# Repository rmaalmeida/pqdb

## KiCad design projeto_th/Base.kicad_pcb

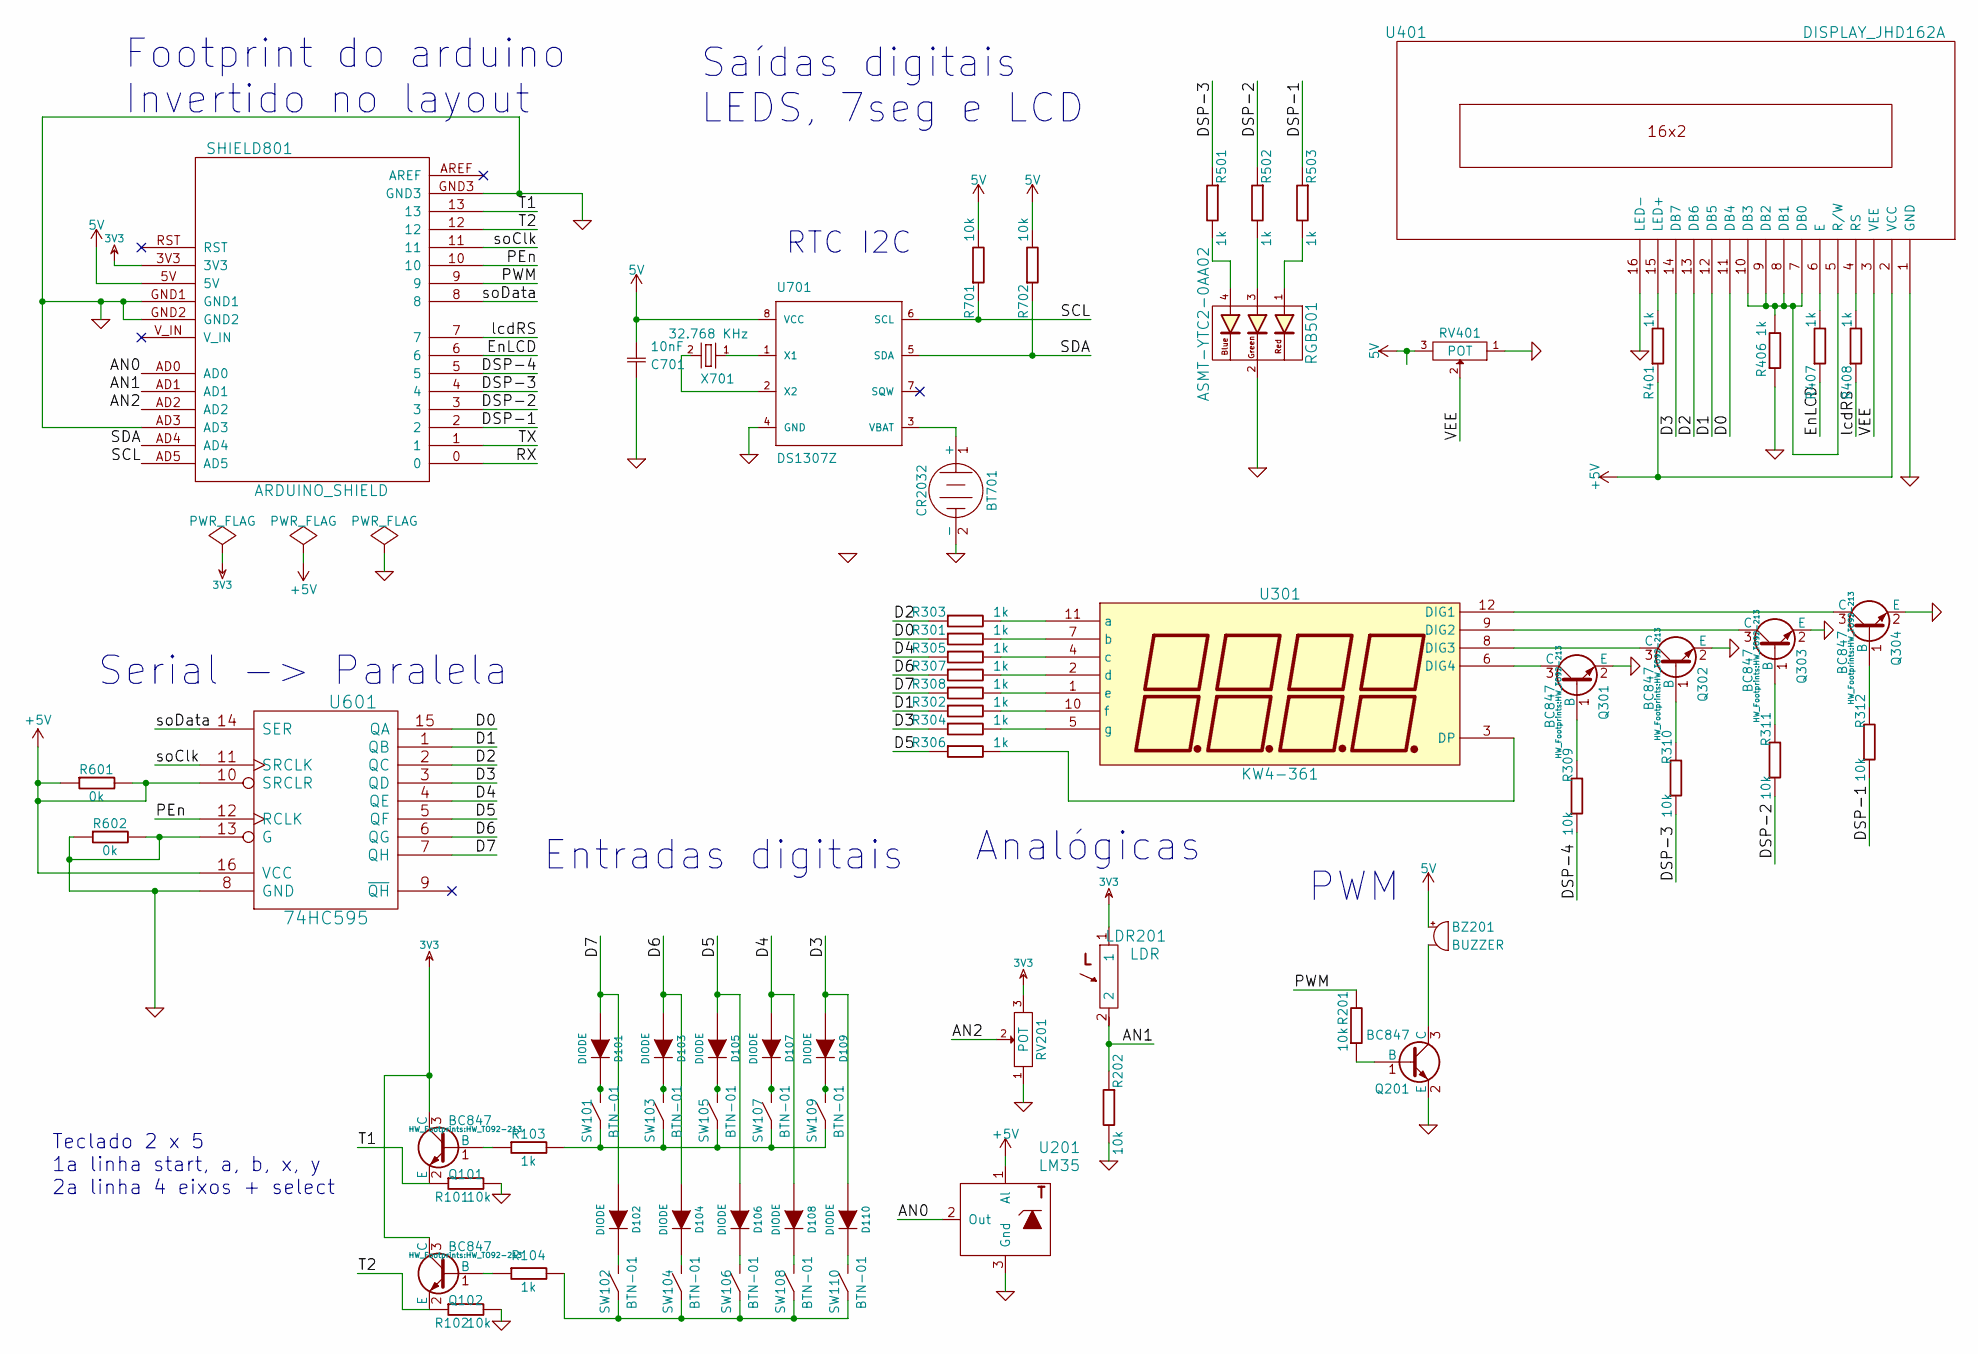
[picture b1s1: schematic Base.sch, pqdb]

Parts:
BT701: CR2032; HW_CR2032H
BZ201: BUZZER; HW_Buzzer
C701: 10nF; HW_CAPACITOR
D101, D102, D103, D104, D105, D106, D107, D108, D109, D110: DIODE; D5
LDR201: LDR; HW_LDR
Q101, Q102, Q201, Q301, Q302, Q303, Q304: BC847; HW_TO92-213
R101, R102, R201, R202, R309, R310, R311, R312, R701, R702: 10k; HW_Resistor
R103, R104, R301, R302, R303, R304, R305, R306, R307, R308, R401, R406, R407, R408, R501, R502, R503: 1k; HW_Resistor
R601, R602: 0k; Resistor_Horizontal_RM15mm
RGB501: ASMT-YTC2-0AA02; HW_LED-5MM-RGB
RV201, RV401: POT; HW_Potenciometro_2
SHIELD801: ARDUINO_SHIELD; ARDUINO_SHIELD_2
SW101, SW102, SW103, SW104, SW105, SW106, SW107, SW108, SW109, SW110: BTN-01; HW_Switch_tactil_adaptada
U201: LM35; HW_TO92-123
U301: KW4-361; HW_Disp_7seg_4dig
U401: DISPLAY_JHD162A; HW_LCD
U601: 74HC595; HW_DIP-16__300_ELL
U701: DS1307Z; HW_DIP-8
X701: 32.768 KHz; HW_Crystal_32768

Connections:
3V3: LDR201.1, Q101.3 (C), Q102.3 (C), RV201.3, SHIELD801.3V3
/AN0: SHIELD801.AD0, U201.2 (Out)
/AN1: LDR201.2, R202.1, SHIELD801.AD1
/AN2: RV201.2, SHIELD801.AD2
/D0: R301.1, U401.11 (DB4), U601.15 (QA)
/D1: R302.1, U401.12 (DB5), U601.1 (QB)
/D2: R303.1, U401.13 (DB6), U601.2 (QC)
/D3: D109.1 (A), D110.1 (A), R304.1, U401.14 (DB7), U601.3 (QD)
/D4: D107.1 (A), D108.1 (A), R305.1, U601.4 (QE)
/D5: D105.1 (A), D106.1 (A), R306.1, U601.5 (QF)
/D6: D103.1 (A), D104.1 (A), R307.1, U601.6 (QG)
/D7: D101.1 (A), D102.1 (A), R308.1, U601.7 (QH)
/DSP-1: R312.1, R503.1, SHIELD801.2
/DSP-2: R311.1, R502.1, SHIELD801.3
/DSP-3: R310.1, R501.1, SHIELD801.4
/DSP-4: R309.1, SHIELD801.5
/EnLCD: R407.1, SHIELD801.6
/PEn: SHIELD801.10, U601.12 (RCLK)
/PWM: R201.2, SHIELD801.9
/RX: SHIELD801.0
/SCL: R701.1, SHIELD801.AD5, U701.6 (SCL)
/SDA: R702.1, SHIELD801.AD4, U701.5 (SDA)
/T1: Q101.2 (E), R101.1, SHIELD801.13
/T2: Q102.2 (E), R102.1, SHIELD801.12
/TX: SHIELD801.1
/VEE: RV401.2, U401.3 (VEE)
/lcdRS: R408.1, SHIELD801.7
/soClk: SHIELD801.11, U601.11 (SRCLK)
/soData: SHIELD801.8, U601.14 (SER)
GND: BT701.2 (-), C701.1, Q201.2 (E), Q301.2 (E), Q302.2 (E), Q303.2 (E), Q304.2 (E), R101.2, R102.2, R202.2, R406.1, R602.1, R602.2, RGB501.2 (KG), RV201.1, RV401.1, SHIELD801.AD3, SHIELD801.GND1, SHIELD801.GND2, SHIELD801.GND3, U201.3 (Gnd), U401.1 (GND), U401.16 (LED-), U601.8 (GND), U601.13 (G), U701.4 (GND)
unnamed: BT701.1 (+), U701.3 (VBAT)
unnamed: BZ201.2, Q201.3 (C)
unnamed: D101.2 (K), SW101.2
unnamed: D102.2 (K), SW102.2
unnamed: D103.2 (K), SW103.2
unnamed: D104.2 (K), SW104.2
unnamed: D105.2 (K), SW105.2
unnamed: D106.2 (K), SW106.2
unnamed: D107.2 (K), SW107.2
unnamed: D108.2 (K), SW108.2
unnamed: D109.2 (K), SW109.2
unnamed: D110.2 (K), SW110.2
unnamed: Q101.1 (B), R103.1
unnamed: Q102.1 (B), R104.1
unnamed: Q201.1 (B), R201.1
unnamed: Q301.1 (B), R309.2
unnamed: Q301.3 (C), U301.6 (DIG4)
unnamed: Q302.1 (B), R310.2
unnamed: Q302.3 (C), U301.8 (DIG3)
unnamed: Q303.1 (B), R311.2
unnamed: Q303.3 (C), U301.9 (DIG2)
unnamed: Q304.1 (B), R312.2
unnamed: Q304.3 (C), U301.12 (DIG1)
unnamed: R103.2, SW101.1, SW103.1, SW105.1, SW107.1, SW109.1
unnamed: R104.2, SW102.1, SW104.1, SW106.1, SW108.1, SW110.1
unnamed: R301.2, U301.7 (b)
unnamed: R302.2, U301.10 (f)
unnamed: R303.2, U301.11 (a)
unnamed: R304.2, U301.5 (g)
unnamed: R305.2, U301.4 (c)
unnamed: R306.2, U301.3 (DP)
unnamed: R307.2, U301.2 (d)
unnamed: R308.2, U301.1 (e)
unnamed: R401.2, U401.15 (LED+)
unnamed: R406.2, U401.5 (R/W), U401.7 (DB0), U401.8 (DB1), U401.9 (DB2), U401.10 (DB3)
unnamed: R407.2, U401.6 (E)
unnamed: R408.2, U401.4 (RS)
unnamed: R501.2, RGB501.4 (AB)
unnamed: R502.2, RGB501.3 (AG)
unnamed: R503.2, RGB501.1 (AR)
unnamed: U701.1 (X1), X701.1
unnamed: U701.2 (X2), X701.2

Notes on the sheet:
RTC I2C
Saídas digitais LEDS, 7seg e LCD
Teclado 2 x 5 1a linha start, a, b, x, y 2a linha 4 eixos + select
Analógicas
PWM
Serial -> Paralela
Footprint do arduino Invertido no layout
Entradas digitais

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
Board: 2 copper layers, 68 parts (2 on the bottom side), 71 nets, no tracks yet.

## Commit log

2016-11-21 :tada: Added .gitattributes & .gitignore files
2017-03-18 pqdb
    1st version through hole
2017-03-18 Base project of pqdb
2017-03-18 Revert "pqdb"
    This reverts commit 2603acf2611178a825194f66c1febb466036f04d.
